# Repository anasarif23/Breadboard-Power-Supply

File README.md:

# Breadboard Power Supply

A dual-rail regulated power supply module for solderless breadboards, designed in KiCad. It takes a 12V barrel-jack input and provides two independently selectable output rails (5V or 3.3V) to power breadboard projects.

## Overview

This board regulates a 12V DC input down to clean 5V and 3.3V rails using an **LM7805** (fixed 5V) and an **LM317** (adjustable, set to 3.3V), then routes the selected voltage to two separate output rails — a "top" rail and a "bottom" rail — matching the standard dual power-rail layout on a breadboard. Each rail's voltage is chosen independently via a jumper selector, and power is switched at the barrel jack with an LED indicator to show when the board is live.

## Features

- 12V DC barrel-jack input with integrated switch
- Two independent output rails (top and bottom), each individually selectable between **5V** and **3.3V**
- Fixed 5V regulation via LM7805
- Adjustable regulation (set to 3.3V) via LM317 with resistor divider
- Power-on LED indicator
- Outputs available both as breadboard-pin headers and screw terminals (for jumper wire connections)

## Specifications

| Parameter          | Value                            |
|---------------------|-----------------------------------|
| Input Voltage       | 12V DC (barrel jack)             |
| Output Voltage(s)   | 5V and 3.3V (independently selectable per rail) |
| Regulators          | LM7805 (TO-220, fixed 5V), LM317 (TO-220, adjustable) |
| Indicator           | Power LED (D1) |
| Output Connectors   | Breadboard pin headers (J2, J4) + screw terminals (J5, J6) |

## Bill of Materials (from schematic)

| Ref | Part | Value / Type |
|-----|------|---------------|
| U1  | LM7805_TO220 | Fixed 5V linear regulator |
| U2  | LM317_TO-220 | Adjustable linear regulator |
| J7  | Barrel_Jack_Switch | 12V power input with integrated switch |
| SW1 | EG1218 | Rail on/off switch |
| D1  | LED | Power indicator |
| C1  | 0.1 µF | Input decoupling capacitor |
| C2  | 10 µF | Output filter capacitor (LM7805 side) |
| C3  | 1 µF | Output filter capacitor (LM317 side) |
| R1  | 330 Ω | LM317 voltage-set divider |
| R2  | 330 Ω | LM317 voltage-set divider |
| R3  | 560 Ω | LM317 voltage-set divider (sets ADJ for 3.3V output) |
| J3  | Conn_01x03 | Output Voltage Selector 1 (top rail: 5V / 3.3V) |
| J8  | Conn_01x03 | Output Voltage Selector 2 (bottom rail: 5V / 3.3V) |
| J2  | Conn_01x02 | Output to breadboard (top rail) |
| J4  | Conn_01x02 | Output to breadboard (bottom rail) |
| J5  | Screw_Terminal_01x02 | Output to jumper wires (top rail) |
| J6  | Screw_Terminal_01x02 | Output to jumper wires (bottom rail) |

## Wiring / Setup

1. Connect a 12V DC power adapter to the barrel jack (J7).
2. Use the voltage selector headers (J3 for the top rail, J8 for the bottom rail) to choose 5V or 3.3V independently for each rail.
3. Flip the switch (SW1) to power on — the LED (D1) will light up to confirm the board is live.
4. Take output either by:
   - Plugging the board's pin headers (J2, J4) directly into the breadboard's power rails, or
   - Wiring from the screw terminals (J5, J6) using jumper wires.

> ⚠️ **Warning:** Double-check the jumper position on J3/J8 before connecting sensitive components — selecting the wrong rail voltage could damage 3.3V-only devices.

## Files in This Repository

| File | Description |
|------|-------------|
| `BreadBoardPowerSchematic.pdf` | Exported circuit schematic |
| `BreadBoardPCB-Design.pdf` | PCB layout |
| `gerbers/` | Gerber manufacturing files for fabrication |
| `BreadBoardPower-3dPic.png` | 3D render of the assembled PCB |
| `BreadBoardPower-3dPic1.png` | 3D render of the assembled PCB (alternate view) |
| `BreadBoardPower-3dPic2.png` | 3D render of the assembled PCB (alternate view) |

## Preview

## Design Tool

Designed in **KiCad EDA 10.0.1**.

## License

*(Specify your license here, e.g. MIT, CC-BY-SA 4.0, etc.)*

## Author

**anasarif23**

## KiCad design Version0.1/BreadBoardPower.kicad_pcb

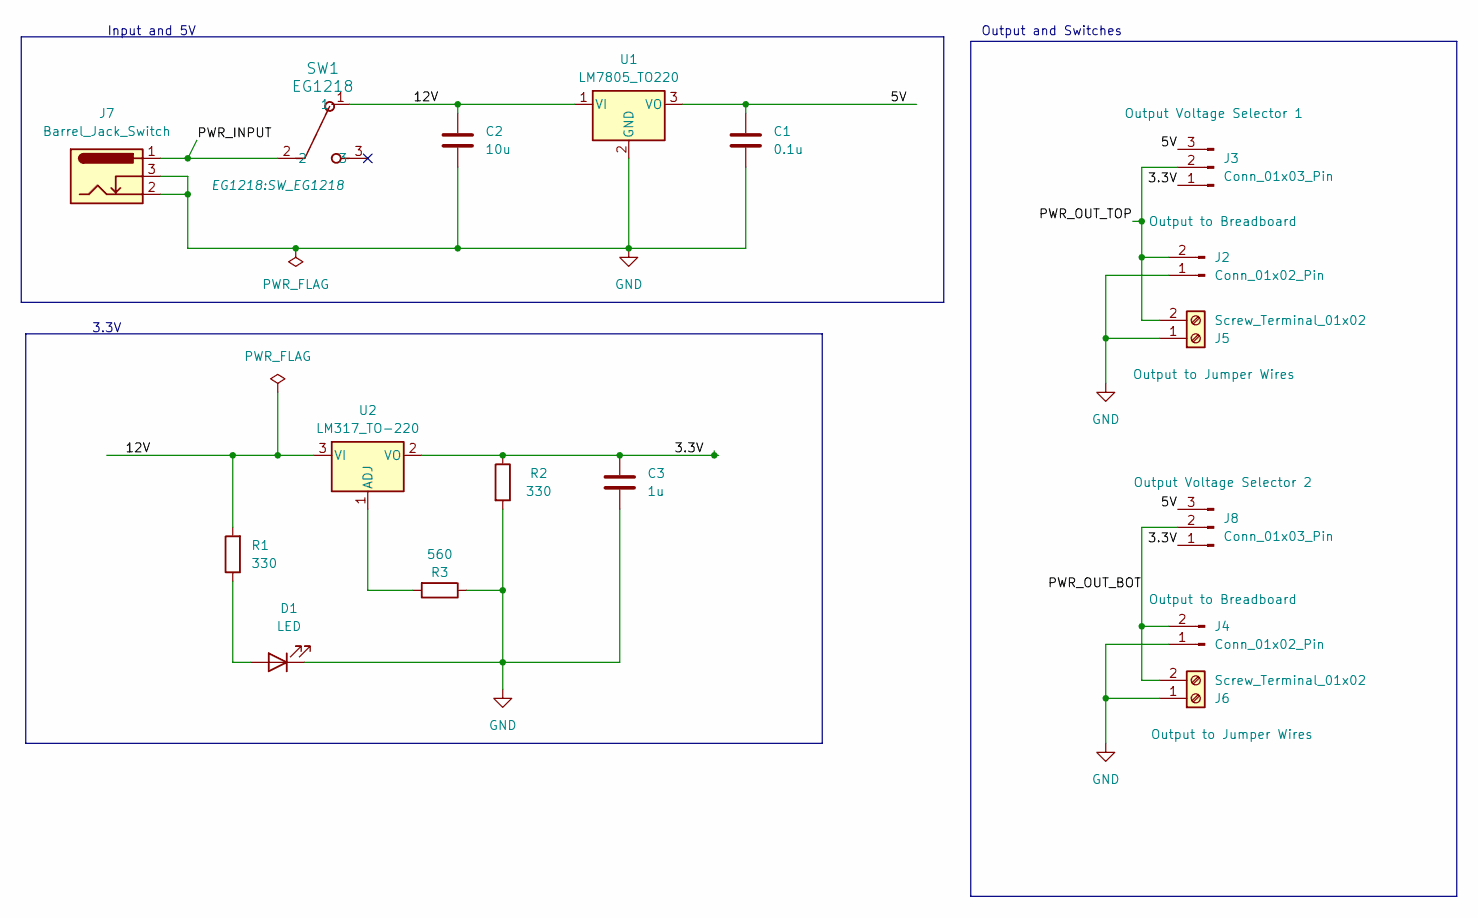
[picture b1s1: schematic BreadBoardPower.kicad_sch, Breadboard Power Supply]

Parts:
C1: 0.1u; C_Disc_D3.0mm_W1.6mm_P2.50mm
C2: 10u; C_Disc_D3.0mm_W1.6mm_P2.50mm
C3: 1u; C_Disc_D3.0mm_W1.6mm_P2.50mm
D1: LED; LED_Rectangular_W5.0mm_H5.0mm
J2, J4: Conn_01x02_Pin; PinHeader_1x02_P2.54mm_Vertical
J3, J8: Conn_01x03_Pin; PinHeader_1x03_P2.54mm_Vertical
J5, J6: Screw_Terminal_01x02; TerminalBlock_MaiXu_MX126-5.0-02P_1x02_P5.00mm
J7: Barrel_Jack_Switch; BarrelJack_Horizontal
R1, R2: 330; R_Axial_DIN0204_L3.6mm_D1.6mm_P7.62mm_Horizontal
R3: 560; R_Axial_DIN0204_L3.6mm_D1.6mm_P7.62mm_Horizontal
SW1: EG1218; SW_EG1218
U1: LM7805_TO220; TO-220-3_Vertical
U2: LM317_TO-220; TO-220-3_Vertical

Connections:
/3.3V: C3.1, J3.1, J8.1, R2.1, U2.2 (VO)
/5V: C1.1, J3.3, J8.3, U1.3 (VO)
/12V: C2.1, R1.2, SW1.1, U1.1 (VI), U2.3 (VI)
/PWR_INPUT: J7.1, SW1.2
/PWR_OUT_BOT: J4.2, J6.2, J8.2
/PWR_OUT_TOP: J2.2, J3.2, J5.2
GND: C1.2, C2.2, C3.2, D1.1 (K), J2.1, J4.1, J5.1, J6.1, J7.2, J7.3, R2.2, R3.1, U1.2 (GND)
unnamed: D1.2 (A), R1.1
unnamed: R3.2, U2.1 (ADJ)

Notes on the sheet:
Output and Switches
3.3V
Input and 5V

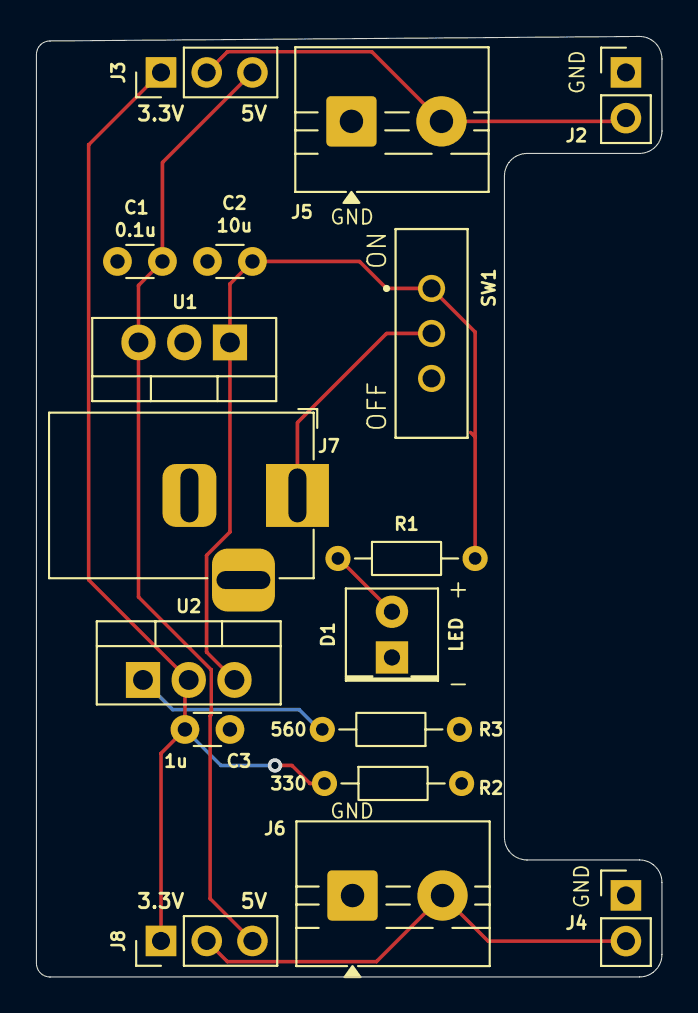
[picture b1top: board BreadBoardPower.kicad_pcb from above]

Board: 2 copper layers, 34.8 x 52.2 mm, 17 parts (0 on the bottom side), 9 nets.
